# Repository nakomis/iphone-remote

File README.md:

# iphone-remote — A coin-cell BLE trigger fob for a custom iPhone camera app

## Support

If you find this useful, please consider buying me a coffee:

## Table of Contents

<!-- toc -->

- [What it is](#what-it-is)
- [Architecture Diagram](#architecture-diagram)
- [Repository Layout](#repository-layout)
- [Architecture Diagrams](#architecture-diagrams)
- [Support](#support)

<!-- tocstop -->

## What it is

A car-key-sized fob with one button. Press it and a custom iPhone camera app,
about six feet away, takes a photo. An LED on the fob flashes when the phone
acknowledges the press.

- **Radio:** advertising-only Bluetooth Low Energy. No pairing, no connection.
  The fob wakes on a press, broadcasts a short burst of adverts, listens briefly
  for an acknowledgement advert from the phone, and goes back to sleep.
- **Power:** a CR2032 coin cell, for years.
- **Chip:** Nordic nRF52810 (QFN-32), on a 2-layer board assembled by JLCPCB
  using their Economic (single-sided) service.
- **Several fobs, one phone:** three solder jumpers set a fob ID from 0 to 7.

The full design is in [`docs/superpowers/specs/`](docs/superpowers/specs/).

## Architecture Diagram

## Repository Layout

| Path | Contents |
|---|---|
| `hardware/` | KiCad project: schematic, PCB, BOM and placement files for JLCPCB |
| `firmware/` | nRF Connect SDK (Zephyr) firmware for the nRF52810 |
| `docs/superpowers/specs/` | Design document and over-the-air protocol |
| `docs/architecture/` | Architecture diagram source (draw.io) |
| `docs/logo-candidates/` | Logo candidates awaiting a verdict |

## Architecture Diagrams

`docs/architecture/iphone-remote.drawio` is the source for the diagram above.
The SVG is auto-regenerated on commit by the pre-commit hook in `.githooks/pre-commit`.

To activate the hook after cloning:

```bash
git config core.hooksPath .githooks
```

## Support

If you find this useful, please consider buying me a coffee:

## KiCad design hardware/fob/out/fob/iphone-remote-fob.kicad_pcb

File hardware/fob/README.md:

# Fob board

The trigger fob's PCB, generated by code from the circuit outward. The pipeline is adapted from
tinycrypt's `hardware/key-board` (circuit as Python, EasyEDA footprints via easyeda2kicad,
Freerouting, KiCad DRC, then JLCPCB fab files). The design is in
[`docs/superpowers/specs/2026-11-05-iphone-remote-fob-design.md`](../../docs/superpowers/specs/2026-11-05-iphone-remote-fob-design.md).

**Stage:** laid out and DRC-clean (IREM-4). Next: JLC quote (IREM-5).

## Build

```bash
ASDF_PYTHON_VERSION=3.11.15 python -m venv .venv
.venv/bin/pip install -r requirements.txt
./fetch_parts.sh             # only if footprints/ is missing or a part is added (resumable)
mkdir -p freerouting && cp <somewhere>/freerouting-2.5.0.jar freerouting/   # Java via asdf
.venv/bin/python build.py --route   # full route log: /tmp/irem-fob-route.log
.venv/bin/python -m pytest
```

There's no drawn schematic: `board/fob_board.py` *is* the schematic, and `out/fob/netlist.txt`
lists every net. Comments in it carry Nordic's reference designators (C1 to C10, L1 to L3, X1)
so it can be checked line by line against Nordic's "QCAA QFN32 with DC/DC regulator setup".

## Circuit

| Ref | Part | Notes |
|---|---|---|
| U1 | nRF52810-QCAA-R (C519278) | QFN-32, 0.5 mm pitch |
| BT1 | MY-2032-12 CR2032 holder (C964833) | side clips +, centre pad − |
| C11 | 22 µF 0805 | bulk, at the holder |
| C9, C5, C8 | 4.7 µF, 100 nF, 100 nF | VDD pins 32, 9, 25 |
| C4, C7 | 100 nF, 100 pF | DEC1, DEC3; DEC2 not connected (Nordic C6 N.C.) |
| L2, L3, C10 | 10 µH, 15 nH, 1 µF | DC/DC: DCC → L2 → L3 → DEC4 |
| Y1, C1, C2 | 32 MHz CL 8 pF (C718072), 12 pF ×2 | |
| C3, L1 | 0.8 pF shunt, 3.9 nH series | Nordic's match → 50 Ω `RF` |
| CA1, R3, CA2 | DNP, 0 Ω, DNP | π footprint for retuning the antenna by hand |
| AE1 | Johanson 2450AT18D0100002E (C17410360) | pad 1 feed, 2–4 GND (fed from the left) |
| SW1, R2 | TS-1187A (C318884), 1 MΩ pull-up | P0.06, active low |
| D1, R1 | red 0603 LED (C2286), 470 Ω | P0.09, active high |
| JP1–JP3 | solder jumpers to GND | P0.12 / P0.14 / P0.15 = ID bits 0 / 1 / 2 |
| J1 | Tag-Connect TC2030 (legged) | 1 VBAT, 2 SWDIO, 3 nRESET (P0.21), 4 SWDCLK, 5 GND, 6 SWO (P0.18) |
| J2 | 2×6 1.27 mm header, **not fitted** | 1 VBAT, 2 GND, 3 P0.25, 4 P0.00, 5 P0.28, 6 P0.01, 7 P0.30, 8 P0.04, 9 P0.16, 10 P0.05, 11 P0.20, 12 P0.10 (ordered to suit the routing) |

22 parts are assembled, with 7 extended parts. Every LCSC part was checked as in stock and
"Economic and Standard" on its JLC page on 5 Nov 2026.

## Layout (IREM-4)

`build.py --route` writes `out/fob/`: the board (`iphone-remote-fob.kicad_pcb`), `drc.json`,
`bom.csv`, `cpl.csv`, the gerbers zip, top and bottom renders, and
`iphone-remote-fob-outline.dxf` (board edge + courtyards, for the case). Fab files are written
only when KiCad's DRC has no errors and nothing unconnected. Freerouting isn't deterministic;
rerun if a run leaves something open.

- **Board:** 29 × 47 mm, 2 layers, 1.6 mm, every part on top. Antenna on the top edge, the
  nRF52810 just below it with the TC2030 to its right, the unpopulated breakout under the chip,
  the ID jumpers (labelled 1 / 2 / 4) under the TC2030, button and LED below, the CR2032 at the
  far end.
- **Hand-routed** (`board/fob_layout.py`, `rf_hand_route`): the RF chain, crystal, DEC1/3/4, the
  DC/DC, VDD to its three caps, escapes to vias for the pins the router couldn't reach, and the
  TC2030 fan-out (one track per gap between its leg holes, to vias outside them). Freerouting
  does the rest.
- **B.Cu kept solid** under the chip and under the RF line (router keep-outs), with nine vias in
  the chip's exposed pad and GND stitching on a 1.5 mm grid elsewhere.
- **Every GND pad joins the pour solidly** (no thermal spokes).
- **Courtyard overlaps are warnings, not errors** (`kicad_pcb.py` rule severities): the 0402s
  round the QFN sit inside its generous courtyard by design.
- The remaining warnings are silk overlaps and one unused fan-out via.

## Layout rules (from the antenna datasheet)

- **Antenna** (Johanson datasheet, evaluation-board layout): edge-mounted, on the board edge,
  with **no copper on any layer** in a 4.0 × 6.0 mm area around it (pads plus 4.1 mm into the
  board). No battery or metal under it. Grounded-coplanar 50 Ω feed through the R3/CA1/CA2 π.
- Put the antenna at the end away from the button and the CR2032 holder.
- Everything on the top side (JLC Economic). The bottom is ground pour.

## Footprint notes

- `fetch_parts.sh` hit EasyEDA's rate limit for four basic two-pin passives (C1035, C27143,
  C25117, C26083). They use already-fetched footprints of the same package (C0603, L0402,
  R0402), with pin name = pad number, which is all a two-pin part needs.
- The EasyEDA symbols type every pin "unspecified", so `check()` can't catch an unconnected
  power pin; `tests/test_fob_board.py` checks every nRF52810 pad explicitly.
- `footprints/local.pretty` holds KiCad 10 stock footprints: the TC2030 legged footprint, the
  solder jumper and the 2×6 1.27 mm header.

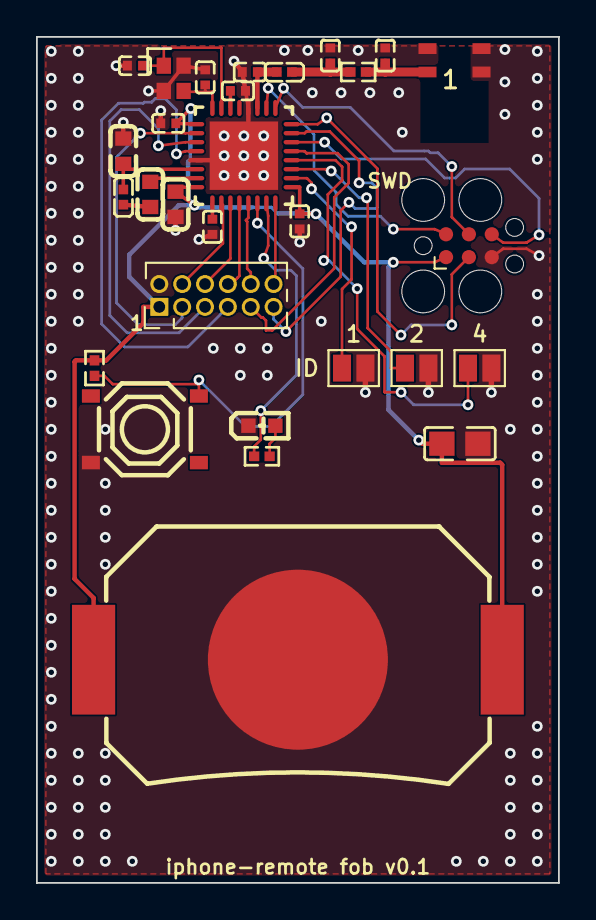
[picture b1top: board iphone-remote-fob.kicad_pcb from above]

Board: 2 copper layers, 29.0 x 47.0 mm, 30 parts (1 on the bottom side), 32 nets.

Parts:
AE1: 2450AT18D0100E; ANT-SMD_4P-L3.2-W1.6
ART1: ART1
BT1: MY-2032-12; BAT-SMD_MY-2032-12
C1, C2: 12pF; C0402
C3: 0.8pF; C0402
C4, C5, C8: 100nF; C0402
C7: 100pF; C0402
C9: 4.7uF; C0603
C10: 1uF; C0603
C11: 22uF; C0805
CA1, CA2: DNP; C0402
D1: KT-0603R red; LED-SMD_L1.6-W0.8-R-RD
J1: TC2030-CTX (SWD); Tag-Connect_TC2030-IDC-FP_2x03_P1.27mm_Vertical
J2: 2x6 1.27mm (unpopulated); PinHeader_2x06_P1.27mm_Vertical
JP1, JP2, JP3: Solder jumper; SolderJumper-2_P1.3mm_Open_Pad1.0x1.5mm
L1: 3.9nH; L0402
L2: 10uH; C0603
L3: 15nH; L0402
R1: 470R; R0402
R2: 1M; R0402
R3: 0R; R0402
SW1: TS-1187A-B-A-B; SW-SMD_4P-L5.1-W5.1-P3.70-LS6.5-TL_H1.5
U1: nRF52810-QCAA-R; QFN-32_L5.0-W5.0-P0.50-BL-EP3.8
Y1: 32MHz CL8pF; CRYSTAL-SMD_4P-L2.0-W1.6-BL

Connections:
ANT: C3.1, L1.1, U1.19
ANT_FEED: AE1.1, CA2.1, R3.2
DCC: L2.1, U1.31
DCDC_L: L2.2, L3.1
DEC1: C4.1, U1.1
DEC3: C7.1, U1.22
DEC4: C10.1, L3.2, U1.30
GND: AE1.2, AE1.3, AE1.4, BT1.2, C1.2, C2.2, C3.2, C4.2, C5.2, C7.2, C8.2, C9.2, C10.2, C11.2, CA1.2, CA2.2, D1.2, J1.5, J2.2, JP1.2, JP2.2, JP3.2, SW1.3, U1.20, U1.29, U1.33, Y1.2, Y1.4
LED_A: D1.1, R1.2
NRESET: J1.3, U1.16
P0_00: J2.4, U1.2
P0_01: J2.6, U1.3
P0_04: J2.8, U1.4
P0_05: J2.10, U1.5
P0_06: R2.1, SW1.2, U1.6
P0_09: R1.1, U1.7
P0_10: J2.12, U1.8
P0_12: JP1.1, U1.10
P0_14: JP2.1, U1.11
P0_15: JP3.1, U1.12
P0_16: J2.9, U1.13
P0_20: J2.11, U1.15
P0_25: J2.3, U1.26
P0_28: J2.5, U1.27
P0_30: J2.7, U1.28
RF: CA1.1, L1.2, R3.1
SWDCLK: J1.4, U1.17
SWDIO: J1.2, U1.18
SWO: J1.6, U1.14
VBAT: BT1.1, C5.1, C8.1, C9.1, C11.1, J1.1, J2.1, R2.2, U1.9, U1.25, U1.32
XC1: C1.1, U1.23, Y1.1
XC2: C2.1, U1.24, Y1.3

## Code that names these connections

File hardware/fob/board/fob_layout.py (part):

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
W, L = 29.0, 47.0

# nRF52810 centre; its top pad row (17..24) faces the antenna, ANT (pin 19) at x + 0.75.
UX, UY = 11.5, 6.6
# Antenna: pad 1 (feed) at (AX - 1.5, AY + 0.65), pads 2-4 GND. The RF line runs at y = RF_Y.
AX, AY = 23.2, 1.3
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# bottom row 1..8 at y 9.25, right column 16..9 top to bottom at x 14.15.
AT = {
    "U1": (UX, UY, 0),
    # RF along the top edge: the ANT pin rises to the line at C3 (0.8 pF shunt, Nordic's match),
    # then L1 (3.9 nH) in series, then the tuning pi CA1 / R3 / CA2 (shunts above the line, not
    # fitted) and the antenna's feed pad.
    "C3": (11.83, RF_Y, 180), "L1": (13.75, RF_Y, 0),
    "CA1": (16.3, round(RF_Y - 0.92, 3), 90), "R3": (17.85, RF_Y, 0),
    "CA2": (19.35, round(RF_Y - 0.92, 3), 90), "AE1": (AX, AY, 0),
    # DEC3 (pin 22) cap straight above its pin, GND end above VSS (pin 20)
    "C7": (11.17, 3.0, 0),
    # crystal, its load caps, and VDD pin 25's cap, top left
    "Y1": (7.6, 2.3, 270), "C1": (5.45, 1.6, 180), "C2": (9.35, 2.25, 90),
    "C8": (7.3, 4.8, 180),
    # DC/DC and VDD pin 32, bottom left: DEC4 lane (pin 30) to C10 and L3, DCC lane (pin 31) to L2
    "C10": (4.8, 6.35, 90), "L2": (6.3, 8.75, 270), "L3": (4.8, 8.9, 90), "C9": (7.7, 9.3, 270),
    # DEC1 (pin 1) below; VDD pin 9 to the right
    "C4": (9.75, 10.55, 270), "C5": (14.6, 10.25, 270),
    # SWD on the right; the breakout under the chip, its pins in a row along x
    "J1": (24.0, 11.6, 0), "J2": (6.8, 15.0, 90),
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

RF_W = 0.5            # short (< 6 mm) RF runs between 0402 pads; ground pour either side
PIN_W = 0.25          # ANT pin escape: the QFN pad width, so it clears pins 18 and 20


def _segments(net, layer, pts, width):
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    # RF: riser at the pin's own width, then RF_W
    p19, c3, l1a, l1b = P("U1", "19"), P("C3", "1"), P("L1", "1"), P("L1", "2")
    r3a, r3b, ca1, ca2, feed = P("R3", "1"), P("R3", "2"), P("CA1", "1"), P("CA2", "1"), P("AE1", "1")
    t += _segments("ANT", "F.Cu", [p19, (p19[0], c3[1])], PIN_W)
    t += _segments("ANT", "F.Cu", [c3, l1a], RF_W)
    t += _segments("RF", "F.Cu", [l1b, (ca1[0], RF_Y), r3a], RF_W) + _segments("RF", "F.Cu", [(ca1[0], RF_Y), ca1], RF_W)
    t += _segments("ANT_FEED", "F.Cu", [r3b, (ca2[0], RF_Y), feed], RF_W)
    t += _segments("ANT_FEED", "F.Cu", [(ca2[0], RF_Y), ca2], RF_W)
    w = 0.15
    # DEC3 up to C7; C7's GND end down to VSS pin 20, and across to C3's GND end and a via
    p22, c7a, c7b, p20, c3g = P("U1", "22"), P("C7", "1"), P("C7", "2"), P("U1", "20"), P("C3", "2")
    t += _segments("DEC3", "F.Cu", [p22, c7a], 0.2)
    gv = Via("GND", 10.95, 1.35)
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    t += _segments("VBAT", "F.Cu", [p25, c8a], 0.2) + _segments("GND", "F.Cu", [c8b, (c8v.x, c8v.y)], 0.25)
    v.append(c8v)
    # P0.25 / P0.28 / P0.30 escape left to staggered vias (the router carries them on from there)
    for pin, net, (vx, vy) in (("26", "P0_25", (5.75, 5.35)), ("27", "P0_28", (6.75, 6.05)), ("28", "P0_30", (7.75, 6.5))):
        pp = P("U1", pin)
        t += _segments(net, "F.Cu", [pp, (round(pp[0] - 0.6, 3), pp[1]), (vx, vy)], w)
        v.append(Via(net, vx, vy))
    # DEC4 lane (pin 30) to C10 and L3; DCC lane (pin 31) to L2; L2 to L3; VDD pin 32 to C9
    p30, p31, p32 = P("U1", "30"), P("U1", "31"), P("U1", "32")
    c10a, c10b, l2a, l2b, l3a, l3b = P("C10", "1"), P("C10", "2"), P("L2", "1"), P("L2", "2"), P("L3", "1"), P("L3", "2")
    c9a, c9b = P("C9", "1"), P("C9", "2")
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    c10v, c9v = Via("GND", 4.8, 4.75), Via("GND", 7.7, 10.75)
    t += _segments("GND", "F.Cu", [c10b, (c10v.x, c10v.y)], 0.25) + _segments("GND", "F.Cu", [c9b, (c9v.x, c9v.y)], 0.25)
    v += [c10v, c9v]
    # DEC1 (pin 1) down to C4; VDD pin 9 to C5
    p1, c4a, c4b, p9, c5a, c5b = P("U1", "1"), P("C4", "1"), P("C4", "2"), P("U1", "9"), P("C5", "1"), P("C5", "2")
    t += _segments("DEC1", "F.Cu", [p1, c4a], 0.2)
    t += _segments("VBAT", "F.Cu", [p9, (c5a[0], p9[1]), c5a, (15.5, c5a[1])], 0.2)
    c4v, c5v = Via("GND", 9.0, 11.25), Via("GND", 14.6, 11.4)
    # nRESET (pin 16, top of the right column) escapes right to a via
    p16 = P("U1", "16")
    rv = Via("NRESET", 16.1, 4.5)
    t += _segments("NRESET", "F.Cu", [p16, (15.6, p16[1]), (rv.x, rv.y)], w)
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        jv = Via("GND", g[0], round(g[1] + 1.35, 3))
        t += _segments("GND", "F.Cu", [g, (jv.x, jv.y)], 0.3)
        v.append(jv)
    # GND: pins 20 (by ANT) and 29 (by DEC4) tied straight into the exposed pad
    p29, ep = P("U1", "29"), P("U1", "33")
    t += _segments("GND", "F.Cu", [p20, (p20[0], round(ep[1] - 1.6, 4))], PIN_W)
    t += _segments("GND", "F.Cu", [p29, (round(ep[0] - 1.6, 4), p29[1])], PIN_W)
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
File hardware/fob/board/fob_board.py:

"""iphone-remote fob (IREM-3): nRF52810-QCAA on a CR2032, one button, a red ack LED, three
fob-ID solder jumpers, an unpopulated 2x6 1.27 mm breakout and a Tag-Connect TC2030 SWD footprint.

The circuit follows Nordic's nRF52810 "QCAA QFN32 with DC/DC regulator setup" reference
(docs.nordicsemi.com, ps_nrf52810, Reference circuitry, read 5 Nov 2026); reference designators
in comments (C1..C10, L1..L3, X1) are Nordic's, so the two can be compared line by line. Design
document: docs/superpowers/specs/2026-11-05-iphone-remote-fob-design.md.
"""
from board.netlist import Circuit

GND, VBAT = "GND", "VBAT"

# GPIO assignment (design doc section 4.8). Net names use P0_nn.
BUTTON, LED = "P0.06", "P0.09"
ID_BITS = ("P0.12", "P0.14", "P0.15")          # bit 0, 1, 2
SWO, NRESET = "P0.18", "P0.21/nRESET"
# Breakout header J2: pin 1 VBAT, pin 2 GND, then the ten spare GPIOs on pins 3..12, ordered
# to suit the layout: the even pins (the row nearest the chip) take the chip's bottom-edge GPIOs
# left to right, the odd pins the side GPIOs (left column, then right).
BREAKOUT = ("P0.25", "P0.00/XL1", "P0.28/AIN4", "P0.01/XL2", "P0.30/AIN6", "P0.04/AIN2", "P0.16",
            "P0.05/AIN3", "P0.20", "P0.10")
# TC2030 pin -> net (Tag-Connect TC2030-CTX, ARM Cortex 10-pin mapping).
TC2030_PINS = {"1": VBAT, "2": "SWDIO", "3": "NRESET", "4": "SWDCLK", "5": GND, "6": "SWO"}


def net(pin):
    """Net name for a chip pin name: 'P0.30/AIN6' -> 'P0_30'."""
    return pin.split("/")[0].replace(".", "_")


def _cap(c, key, ref, a, b=GND, dnp=False):
    cap = c.add(key, ref, dnp=dnp)
    c.connect(a, (cap, "1"))
    c.connect(b, (cap, "2"))
    return cap


def build_fob():
    c = Circuit()
    u1 = c.add("NRF", "U1")

    # Power: CR2032 straight onto VDD (1.7-3.6 V, no regulator). The holder's two side clips
    # (pad 1) touch the cell's + can; the centre pad (2) is the cell's - face.
    bt = c.add("BAT", "BT1")
    c.connect(VBAT, (bt, "1"))
    c.connect(GND, (bt, "2"))
    _cap(c, "C22U", "C11", VBAT)                       # bulk, beside the holder (doc 4.3)

    c.connect(VBAT, (u1, "VDD"))
    c.connect(GND, (u1, "VSS"), (u1, "EP"))
    _cap(c, "C4U7", "C9", VBAT)                        # Nordic C9 at VDD pin 32
    _cap(c, "C100N", "C5", VBAT)                       # Nordic C5 at VDD pin 9
    _cap(c, "C100N", "C8", VBAT)                       # Nordic C8 at VDD pin 25
    c.connect("DEC1", (u1, "DEC1"))
    _cap(c, "C100N", "C4", "DEC1")                     # Nordic C4
    c.connect("DEC3", (u1, "DEC3"))
    _cap(c, "C100P", "C7", "DEC3")                     # Nordic C7
    c.no_connect(u1, "DEC2")                           # Nordic C6 is "N.C."

    # DC/DC: DCC -> 10 uH (L2) -> 15 nH (L3) -> DEC4, 1 uF (C10) on DEC4.
    c.connect("DCC", (u1, "DCC"), (c.add("L10U", "L2"), "1"))
    c.connect("DCDC_L", (c.instances["L2"], "2"), (c.add("L15N", "L3"), "1"))
    c.connect("DEC4", (c.instances["L3"], "2"), (u1, "DEC4"))
    _cap(c, "C1U", "C10", "DEC4")

    # 32 MHz crystal (X1, CL 8 pF) with 12 pF load capacitors (C1, C2).
    y1 = c.add("XTAL", "Y1")
    c.connect("XC1", (u1, "XC1"), (y1, "1"))
    c.connect("XC2", (u1, "XC2"), (y1, "3"))
    c.connect(GND, (y1, "GND"))
    _cap(c, "C12P", "C1", "XC1")
    _cap(c, "C12P", "C2", "XC2")

    # RF: Nordic's match, 0.8 pF shunt at ANT (C3) then 3.9 nH series (L1), giving a 50 ohm feed
    # (RF). Then a pi footprint for tuning the chip antenna by hand: shunt (CA1, not fitted),
    # 0 R series (R3), shunt (CA2, not fitted), as Johanson's reference layout allows for.
    c.connect("ANT", (u1, "ANT"))
    _cap(c, "C0P8", "C3", "ANT")
    c.connect("ANT", (c.add("L3N9", "L1"), "1"))
    c.connect("RF", (c.instances["L1"], "2"))
    _cap(c, "CDNP", "CA1", "RF", dnp=True)
    c.connect("RF", (c.add("R0", "R3"), "1"))
    c.connect("ANT_FEED", (c.instances["R3"], "2"))
    _cap(c, "CDNP", "CA2", "ANT_FEED", dnp=True)
    ae = c.add("ANT", "AE1")
    c.connect("ANT_FEED", (ae, "Feed"))
    c.connect(GND, (ae, "GND"))

    # Button to GND with an external 1 M pull-up (internal pull-up off; doc 4.4). The switch's
    # diagonal pads B and C are on different contact bars whichever way the pairs go.
    sw = c.add("SW", "SW1")
    c.connect(net(BUTTON), (u1, BUTTON), (sw, "B"), (c.add("R1M", "R2"), "1"))
    c.connect(VBAT, (c.instances["R2"], "2"))
    c.connect(GND, (sw, "C"))

    # Red LED, high-active through 470 R.
    d1 = c.add("LED", "D1")
    c.connect(net(LED), (u1, LED), (c.add("R470", "R1"), "1"))
    c.connect("LED_A", (c.instances["R1"], "2"), (d1, "A"))
    c.connect(GND, (d1, "K"))

    # Fob ID: three normally-open solder jumpers to GND (closed = 1).
    for bit, pin in enumerate(ID_BITS):
        jp = c.add("JUMPER", f"JP{bit + 1}")
        c.connect(net(pin), (u1, pin), (jp, "1"))
        c.connect(GND, (jp, "2"))

    # SWD: Tag-Connect TC2030 (legged), SWO on P0.18 and nRESET on P0.21.
    j1 = c.add("TC2030", "J1")
    c.connect("SWDIO", (u1, "SWDIO"))
    c.connect("SWDCLK", (u1, "SWDCLK"))
    c.connect("SWO", (u1, SWO))
    c.connect("NRESET", (u1, NRESET))
    for pad, n in TC2030_PINS.items():
        c.connect(n, (j1, pad))

    # Breakout J2 (not fitted by JLC; Martin solders a header when he needs it).
    j2 = c.add("HDR", "J2")
    c.connect(VBAT, (j2, "1"))
    c.connect(GND, (j2, "2"))
    for i, pin in enumerate(BREAKOUT):
        c.connect(net(pin), (u1, pin), (j2, str(i + 3)))
    return c


def pins_h():
    """The firmware header: nRF52810 pin numbers as wired on this board."""
    num = lambda pin: int(pin.split("/")[0].split(".")[1])
    lines = ["/* Generated by hardware/fob/build.py from board/fob_board.py: do not edit. */",
             "#pragma once", "",
             f"#define FOB_PIN_BUTTON {num(BUTTON)}   /* active low, external 1M pull-up */",
             f"#define FOB_PIN_LED {num(LED)}      /* active high, red, 470R */"]
    for bit, pin in enumerate(ID_BITS):
        lines.append(f"#define FOB_PIN_ID_BIT{bit} {num(pin)}  /* jumper to GND, closed = 1 */")
    lines.append("")
    lines.append("/* Breakout J2: pin 1 VBAT, pin 2 GND, then: */")
    for i, pin in enumerate(BREAKOUT):
        lines.append(f"/*   J2.{i + 3}: P0.{num(pin):02d} */")
    return "\n".join(lines) + "\n"
